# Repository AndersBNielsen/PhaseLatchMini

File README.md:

# PhaseLatch Mini – STM32F103 Dual-ADC IQ USB Streamer

> Combined hardware + firmware + host tooling for a compact dual‑ADC I/Q capture platform.

## Overview

High-rate continuous streaming of interleaved dual ADC (I/Q) samples over USB Full‑Speed (FS) using only the built‑in CDC class on an STM32F103C8 ("Blue Pill" style) board. Companion Python host tools provide live visualization, FIFO bridging, raw capture, diagnostics, and throughput benchmarking.

> Status: Actively optimized. Current configured complex sample rate target: **210.5 k I/Q samples/sec** (`IQ_SAMPLE_RATE_HZ` = 210526) with sustained USB payload throughput >500 KiB/s. Timer PSC/ARR are selected at runtime by a search routine for the closest achievable rate; observed effective rate can be within a small delta of the target. ADC sampling time was reduced (now `ADC_SAMPLETIME_28CYCLES_5`) to reach this rate while maintaining conversion stability.

> Origin / Intended Use: Initially developed as a lightweight streaming engine for the [PhaseLoom](https://github.com/AndersBNielsen/PhaseLoom) project, but fully usable with any dual (I/Q) analog front end producing baseband signals on two STM32F1 ADC channels. 
Note: Phaseloom should be modified for best performance. Replace 22kOhm feedback caps with matched 47kOhm resistors and replace the output stage 50 ohms with 0 ohm. 

---
## Hardware: PhaseLatch Mini
A 4‑layer purple PCB (Blue Pill footprint inspired) integrating two SMA input ports and on‑board ~100 kHz low‑pass filtering (~210 kHz complex baseband bandwidth). Designed around the STM32F103C8 in dual regular simultaneous ADC mode (ADC1 + ADC2) to stream interleaved I/Q samples over USB Full-Speed.

### Key Features
- MCU: STM32F103C8 (72 MHz) LQFP‑48
- Dual simultaneous ADC (12‑bit each) packed into 32‑bit words (I lower 12 bits, Q upper 12 bits)
- 2 × edge‑mount SMA (J20 = I_IN, J21 = Q_IN)
- Integrated passive input filtering (inductor + capacitor network targeting ~100 kHz LPF per channel)
- USB‑C connector (USB2.0 FS, CDC class currently; raw/bulk class option planned)
- On‑board 8 MHz + 32.768 kHz crystals for stable system and RTC timing
- Ferrite bead + local bulk/decoupling for cleaner ADC rails
- Unused GPIOs forced to analog mode early for noise reduction (see `Quiet_Unused_Pins` in `main.c`)
- Headers for expansion / SWD / boot configuration

### Production Assets
All fabrication outputs live in `hardware/PhaseLatchMini/production`:
- `PhaseLatchMini.zip` – Gerber/drill bundle ready for PCB fab
- `bom.csv` – Bill of Materials (with LCSC part numbers for quick JLCPCB sourcing)
- `designators.csv` – Component reference list
- `positions.csv` – Pick‑and‑place XY + rotation for SMT assembly
- `netlist.ipc` – IPC netlist export

Direct link (relative): `hardware/PhaseLatchMini/production/PhaseLatchMini.zip`

### BOM Highlights
Representative components (from `bom.csv`):
- Decoupling: multiple 100 nF 0402 caps (C307331) near MCU and filter sections
- Filter / bulk caps: 22 nF, 220 nF, 470 nF mix shaping input response
- Inductors: six 10 µH (0805) parts forming LC sections for each channel’s low‑pass filtering / supply isolation
- USB-C receptacle: 16‑pin (HCTL HC-TYPE-C-16P-01A) with 5k1 CC resistors for proper orientation detection
- Ferrite bead (FB1) for USB / supply noise suppression
- Voltage regulator: MIC5504-3.3 (SOT‑23‑5) providing clean 3V3
- Crystals: 8 MHz main, 32.768 kHz low‑speed (RTC / optional precise timing)
- SMA edge connectors: matched pair for I and Q inputs

### Assembly Notes
- Clean flux residues near high‑impedance analog nodes (C1/C8 cluster) to keep leakage low.
- If performing hand assembly, solder the SMA edge connectors first to anchor board alignment, then USB, then fine‑pitch MCU.

### Filter Tuning
Current passive network targets ~100 kHz corner. For alternative bandwidths:
- Raise corner: decrease shunt capacitance (e.g., swap 470 nF → 220 nF or 22 nF depending on desired slope) or reduce inductance value.
- Lower corner: increase shunt capacitance or employ higher inductance (space permitting). Recalculate fc ≈ 1/(2π√(L·C_eq)).
- Mitigate source‑resistor induced tilt: include its resistance in design equations; keep initial shunt capacitors modest (≤10 nF) if a 50 Ω series is retained upstream.

## Firmware

- Dual ADC synchronous sampling packed as 32-bit little-endian words (I 12-bit + Q 12-bit inside two 16-bit lanes)
- Target sample rate `IQ_SAMPLE_RATE_HZ` (currently 210526) with dynamic TIM3 prescaler/period search (see `timer_trigger_init()` in `iq_adc.c`)
- ADC sampling time set to `ADC_SAMPLETIME_28CYCLES_5` for higher throughput (previous higher value limited rate)
- Circular DMA with half / full transfer interrupts
- Lock-free ring queue feeding USB transmit path
- ISR burst chaining (current chain limit 16 packets per IN completion) to minimize USB idle gaps
- Immediate DMA IRQ packet scheduling ("kick") to prime first packet of each half-buffer
- Optional diagnostic/stat packets suppressed in throughput builds
- Host tools for diagnostics, throughput, raw capture, FIFO bridging, live view

### Changing the Sample Rate
1. Edit `Inc/iq_adc.h` and set `#define IQ_SAMPLE_RATE_HZ <desired_rate>` (I/Q pairs per second).
2. Ensure the new rate is feasible: TIM3 must be able to realize it given 16-bit ARR and prescaler; the search code picks the closest achievable value.
3. If pushing higher rates:
   - Consider reducing ADC sampling time (`ADC_SAMPLETIME_x`) further, but watch noise/performance.
   - Monitor USB throughput counters (`FEED` command) for increased busy skips.
4. Rebuild and flash. Optionally measure actual achieved rate by counting `iq_dma_half_count` + `iq_dma_full_count` over a timed host interval.

### Verifying Achieved Rate
- After START, issue the `A` command periodically; note increments of half/full counts.
- Effective samples/sec ≈ ((delta_half + delta_full) * half_buffer_samples) / time_interval.
- Or capture a known duration with `host_test.py` and compute rows * rate.

---
## Repository Layout

```
platformio.ini              # Build environments & macro flags
src/                        # Firmware sources (USB, ADC, main logic)
Inc/ / include/             # Public headers
host_*.py                   # Python host utilities
lib/ test/                  # (Placeholders / future use)
```

Key firmware files:
- `src/main.c` – System init, main loop USB feeder (fallback scheduling & instrumentation)
- `src/iq_adc.c` / `Inc/iq_adc.h` – ADC+DMA+Timer configuration, DMA IRQ scheduling kick
- `src/usbd_conf.c` – Low-level USB callbacks, DataIn burst chaining logic
- `src/usbd_cdc_if.c` – CDC interface, command parser (A/F/STATS) & data write API
- `src/usbd_raw.c` (future / optional) – Raw class scaffolding (if transitioning from CDC for additional margin)

Host scripts (root directory):
- `host_diagnostics.py` – Passive capture, STATS delta decode, periodic monitor, USB descriptor info
- `host_throughput.py` – PyUSB bulk endpoint benchmark (raw vendor class / future); shows packet stats
- `host_raw_capture.py` – Robust raw USB (PyUSB or CDC) capture with quiet mode & BrokenPipe safety
- `host_iq_fifo.py` – Serial CDC → named FIFO adapter (u8 or cf32) for GQRX / GNU Radio
- `host_iq_live.py` – Terminal live IQ stats + sparklines / averages
- `host_test.py` – Simple START/STOP based capture, optional float32 output & basic stats
- `host_probe.py` – (Currently empty placeholder for future probing utilities)

---
## Build & Flash (PlatformIO)

Prerequisites:
- VS Code + PlatformIO extension (or `pio` CLI)

Clone & open project, then build one of the defined environments:

### PlatformIO Quickstart (Basics)

If you're new to PlatformIO, these are the minimal steps to get a firmware onto the board.

#### Option A: VS Code GUI
1. Install the "PlatformIO IDE" extension in VS Code.
2. Open this project folder (where `platformio.ini` resides).
3. Bottom status bar: pick the desired environment (e.g. `adc`).
4. Click the checkmark (Build). Wait for success.
5. Connect the board via USB (ensure it enumerates) and press the right arrow (Upload). If first flash fails, press/hold BOOT (if available) or use a serial/USB boot jumper sequence depending on your Blue Pill variant.
6. Use the plug icon (Monitor) or run a host script to interact.

#### Option B: CLI
Install PlatformIO Core (Python 3.11+ recommended):
```bash
pip install --upgrade platformio
```
From the project root:
```bash
# List environments defined in platformio.ini
pio run --list-targets

# Build the adc environment
pio run -e adc

# Upload (adjust -e if choosing another env)
pio run -e adc -t upload

# Open a serial monitor (Ctrl+C to exit)
pio device monitor -b 115200
```
If you see permission errors on macOS/Linux, you may need to adjust USB device permissions or add your user to the appropriate group (e.g. `dialout` on some Linux distros).

#### Common Upload Notes
- Some Blue Pill clones require setting/removing BOOT0 jumpers for the built-in ROM bootloader; after initial flash with a USB‑TTL adapter or ST-Link, subsequent USB CDC updates normally proceed automatically.
- For ST-Link users, ensure drivers and udev rules (Linux) are installed.
- If the device does not reset into the new firmware, press the hardware RESET button.

#### Serial Device Identification
On macOS you'll typically see `/dev/tty.usbmodem*`. On Linux, it may appear as `/dev/ttyACM0`. Use `pio device list` to enumerate.

Environments (see `platformio.ini`):
- `env:baseline` – Minimal USB baseline with reduced diagnostics (throughput focus pattern)
- `env:diag` – Heavier diagnostics enabled (ASCII stat chatter)
- `env:adc` – Active dual-ADC streaming (ENABLE_IQ + throughput suppressions)
- `env:adc_smoke` – Lower-intensity validation (extra ADC status prints)

Typical flow (using `env:adc`):
1. Select `adc` environment in PlatformIO
2. Build (should report flash usage ~30%, RAM ~55%)
3. Upload (DFU/serial depending on board configuration)
4. Open a serial monitor or run a host script (e.g. `python host_test.py --progress`)

If enumeration stalls: power cycle board or press reset. Heartbeat LED indicates main loop alive; rapid fallback pattern indicates SysTick/USB early issues.

---
## Runtime Commands (CDC)

Send as ASCII (line ending flexible, CR/LF accepted):
- `START` – Begin IQ streaming (if not already running)
- `STOP` – Halt streaming (host_test.py sends on exit)
- `A` – Print `ADCSTAT` line with ADC & DMA counters
- `F` – Print `FEED` line (USB feeder instrumentation)
- `STATS` – Legacy status snapshot (may be suppressed in throughput builds)

---
## Data Format

Each IQ sample pair is one 32-bit little-endian word composed of two 16‑bit containers produced by the STM32F1 dual regular simultaneous ADC mode:
```
Bits  0..11  : I (ADC1 12-bit result, right-aligned)
Bits 12..15  : Unused (always 0)  <-- upper 4 bits of lower 16-bit half-word
Bits 16..27  : Q (ADC2 12-bit result, right-aligned)
Bits 28..31  : Unused (always 0)  <-- upper 4 bits of upper 16-bit half-word
```

So effectively:
```
uint16_t I_lane = word & 0xFFFF;          // lower half-word
uint16_t Q_lane = (word >> 16) & 0xFFFF;  // upper half-word
uint16_t I_raw12 = I_lane & 0x0FFF;       // mask to 12 bits
uint16_t Q_raw12 = Q_lane & 0x0FFF;
```

The current `host_test.py` treats each 16-bit lane as a full-range unsigned sample and subtracts 32768. That overstates magnitude and uses the high (always zero) 4 bits. For correct 12‑bit centered scaling use:
```
float I = ((int)I_raw12 - 2048) / 2048.0f;   // ≈ [-1.0, +1.0)
float Q = ((int)Q_raw12 - 2048) / 2048.0f;
```
If you need signed 16-bit containers for downstream tooling, you can expand by left-shifting 4 (to occupy high bits) or replicate into 16-bit signed with:
```
int16_t I_s16 = ((int16_t)(I_raw12 ^ 0x800) - 0x800) << 4; // optional dynamic range padding
```
But most host paths should just mask & center at 2048.

---
## ADC / Timing Configuration

- Timer configuration is dynamic: `timer_trigger_init()` iterates prescaler values to find an ARR producing a rate closest to `IQ_SAMPLE_RATE_HZ`.
- Current target: 210526 samples/sec (complex pairs). Achieved rate is printed only via manual inspection (no direct text output yet); you can instrument `(best_rate)` variable in debugger if needed.
- ADC sampling time currently `ADC_SAMPLETIME_28CYCLES_5`; lowering further increases throughput but may degrade SNR and settling for higher source impedances.

Potential Adjustments:
- Increase `IQ_SAMPLE_RATE_HZ` (watch USB bandwidth & chain limit utilization).
- Change ADC sampling time for performance vs accuracy trade-off.
- Raise `chain_limit` (in `usbd_conf.c`) beyond 16 if the queue frequently stalls with residual samples and main loop fallback is minimal.

---
## USB Transfer Strategy & Optimizations
- Chain limit now 16 (see `usbd_conf.c`); README previously referenced 12—updated.
- DMA IRQ kick ensures first packet of each half-buffer is scheduled promptly.
- Remaining headroom: adopt packed 3-byte I12|Q12 mode (roadmap) or vendor RAW class for further rate increases.

---
## Instrumentation & Monitoring

Example FEED output (command `F`):
```
FEED loop=12345 isr=67890 busy=12 chain_max=11
```
Where:
- `loop` – Packets scheduled from main loop (fallback)
- `isr` – Packets scheduled from ISR path (burst + DMA kick)
- `busy` – Attempts skipped because endpoint currently active
- `chain_max` – Highest contiguous packets chained in a single IN completion

ADCSTAT example (`A`):
```
ADCSTAT half=1024 full=1024 drops=0
```
(Exact field names may vary—check live output.)

Use `host_diagnostics.py stats` for legacy STAT delta interpretation, if enabled in build.

---
## Host Utilities

| Script | Purpose |
|--------|---------|
| `host_test.py` | Simple START capture, optional float32 output, stats, graceful Ctrl+C |
| `host_iq_live.py` | Real-time terminal IQ level display, window averages, sparkline |
| `host_iq_fifo.py` | Serial → FIFO converter (u8 or cf32) for GQRX / fifo consumers |
| `host_raw_capture.py` | Raw byte dump with quiet & BrokenPipe-safe pipeline support |
| `host_diagnostics.py` | STATS deltas, passive capture, USB descriptor info |
| `host_throughput.py` | High-rate PyUSB bulk benchmark (raw class future) |
| `host_probe.py` | Placeholder for future probing tools |

### GQRX Integration (via FIFO)
- Set GQRX sample rate to match `IQ_SAMPLE_RATE_HZ` (e.g. 210526) or the nearest supported value.
1. Run FIFO bridge:
   ```
   python3 host_iq_fifo.py --fifo /tmp/iq_cf32.iq
   ```
2. In GQRX, set input to "UDP / File" or external source capable of reading named FIFO (Linux/macOS). Point to `/tmp/iq_cf32.fifo` with sample rate = `210526`.
3. Adjust gain/AGC in GQRX; confirm spectrum updates.

### Live View
```
python host_iq_live.py --port /dev/tty.usbmodemXYZ --window 512 --spark --interval 0.2
```
Shows min/max, window & running averages, and a small ASCII sparkline.

### Raw Capture Example
```
python host_raw_capture.py --out stream.bin --secs 5 --quiet
```
Then post-process with custom scripts or convert to complex floats.

---
## Performance Measurement

Quick rate check (CDC path):
```
python host_test.py --seconds 3 --progress
```
Or FEED counters before & after a timed interval to estimate packet dispatch accumulation.

PyUSB high-rate test (when using/adding raw vendor class):
```
python host_throughput.py --seconds 5 --progress
```

Interpretation updates:
- Bytes/sec ÷ 4 = complex samples/sec (current raw 32-bit mode).
- For future 3-byte packed mode bytes/sec ÷ 3 will apply.

---
## Troubleshooting

| Symptom | Suggestions |
|---------|-------------|
| No `/dev/tty.usbmodem*` device | Replug USB, check cable, ensure board enumerates (dmesg / system log) |
| Streaming stalls after START | Check FEED counters (isr incrementing?). Confirm no flood of diagnostics enabled. |
| Throughput lower than expected | Ensure running `env:adc` (not `diag`), verify chain_max near limit, reduce host-side latency (no heavy printing) |
| Mis-scaled IQ values | Mask to 12 bits (0x0FFF) before centering; ensure not interpreting high unused bits |
| Broken pipe in pipeline capture | Use `host_raw_capture.py --quiet` (handles SIGPIPE and flush safety) |

---
## Roadmap / Future Ideas
- Maintain or push beyond 210 kS/s (USB packing & endpoint tuning)
- Optional tighter 24-bit (3-byte) packing (I12|Q12) – reduces bandwidth ~25%
- Vendor RAW class endpoint for marginal gains over CDC ACM
- Lightweight CRC / sequence tags for host-side drop detection
- Optional AGC / scaling in firmware (convert to centered 16-bit signed)
- Continuous integration tests for host scripts
- IQ gain/phase auto-calibration
- Expanded PhaseLatch Mini variants (higher‑resolution MCUs, external HS USB)

## License

(Choose and add a SPDX license header & file as appropriate, e.g. MIT or Apache-2.0.)

---
## Attribution / Notes

Developed as an incremental exploration of practical FS USB throughput & latency reduction techniques on resource-constrained MCUs while streaming synchronous dual-ADC data.

Contributions / suggestions welcome.

## Getting a PCB

## Production & Manufacturing
- The `hardware/production/` folder includes all needed files. 

This project is kindly sponsored by JLCPCB. They offer cheap, professional looking PCBs and super fast delivery.

Step 1: Get the gerber file zip package from the /hardware folder

Step 2: Upload to JLCPCB [https://jlcpcb.com/?from=Anders_N](https://jlcpcb.com/?from=Anders_N)

Step 3: Pick your color, surface finish and order.

You can use these affiliate links to get a board for $2 and also get $54 worth of New User Coupons at: https://jlcpcb.com/?from=Anders_N

And in case you also want to order a 3D-printed case you can use this link. 
How to Get a $7 3D Printing Coupon: [https://3d.jlcpcb.com/?from=Anders3DP](https://jlc3dp.com/?from=Anders_N)

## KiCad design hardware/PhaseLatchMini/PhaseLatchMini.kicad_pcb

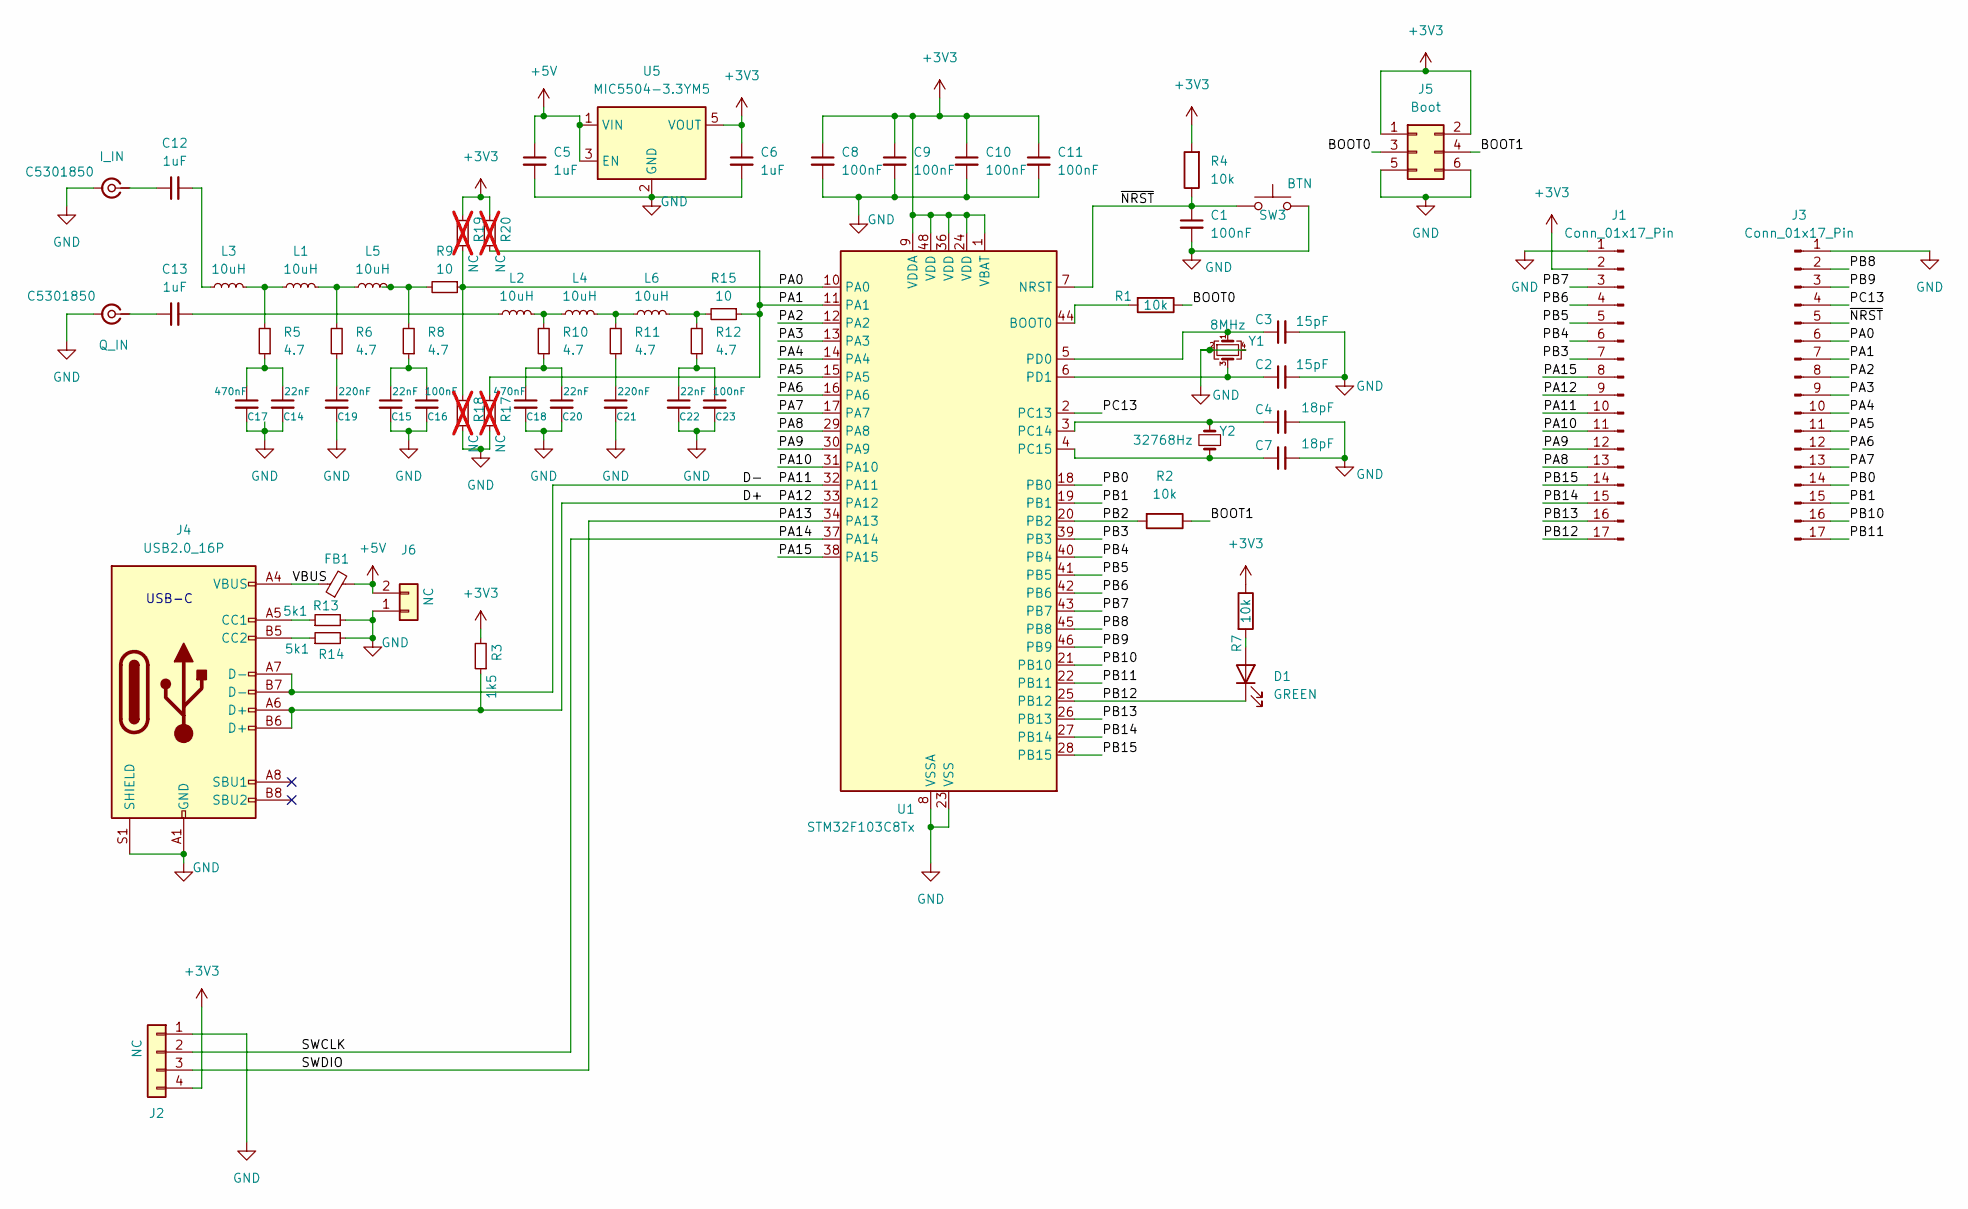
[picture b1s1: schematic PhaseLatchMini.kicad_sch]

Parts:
C1, C8, C9, C10, C11, C16, C23: 100nF; C_0402_1005Metric; LCSC C307331
C2, C3: 15pF; C_0402_1005Metric; LCSC C1548
C4, C7: 18pF; C_0402_1005Metric; LCSC C1549
C5, C6, C12, C13: 1uF; C_0805_2012Metric; LCSC C28323
C14, C15, C20, C22: 22nF; C_0402_1005Metric; LCSC C1532
C17, C18: 470nF; C_0603_1608Metric; LCSC C1623
C19, C21: 220nF; C_0402_1005Metric; LCSC C16772
D1: GREEN; LED_0805_2012Metric; LCSC C2297
FB1: FerriteBead_Small; L_0603_1608Metric; LCSC C14709
J1, J3: Conn_01x17_Pin; PinHeader_1x17_P2.54mm_Vertical
J2: NC; PinHeader_1x04_P2.54mm_Vertical
J4: USB2.0_16P; USB_C_Receptacle_HCTL_HC-TYPE-C-16P-01A; LCSC C2894897
J5: Boot; PinHeader_2x03_P2.54mm_Vertical
J6: NC; PinHeader_1x02_P2.54mm_Vertical
J20: I_IN; SMA_Samtec_SMA-J-P-H-ST-EM1_EdgeMount; LCSC C5301850
J21: Q_IN; SMA_Samtec_SMA-J-P-H-ST-EM1_EdgeMount; LCSC C5301850
L1, L2, L3, L4, L5, L6: 10uH; L_0805_2012Metric; LCSC C1046
R1, R2, R4, R7: 10k; R_0402_1005Metric; LCSC C25744
R3: 1k5; R_0402_1005Metric; LCSC C25867
R5, R6, R8, R10, R11, R12: 4.7; R_0603_1608Metric; LCSC C23164
R9, R15: 10; R_0603_1608Metric; LCSC C22859
R13, R14: 5k1; R_0402_1005Metric; LCSC C25905
R17, R18, R19, R20: NC; R_0402_1005Metric; LCSC C25867; not fitted
SW3: BTN; SW_SPST_TL3342; LCSC C318884
U1: STM32F103C8Tx; LQFP-48_7x7mm_P0.5mm; LCSC C8734
U5: MIC5504-3.3YM5; SOT-23-5; LCSC C3021093
Y1: 8MHz; Crystal_SMD_3225-4Pin_3.2x2.5mm; LCSC C5308002
Y2: 32768Hz; Crystal_SMD_3215-2Pin_3.2x1.5mm; LCSC C32346

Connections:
+3V3: C6.1, C8.1, C9.1, C10.1, C11.1, J1.2, J2.4, J5.1, J5.2, R3.2, R4.2, R7.1, R19.2, R20.2, U1.1 (VBAT), U1.9 (VDDA), U1.24 (VDD), U1.36 (VDD), U1.48 (VDD), U5.5 (VOUT)
+5V: C5.1, FB1.2, J6.2, U5.1 (VIN), U5.3 (EN)
/BOOT0: J5.3, R1.1
/BOOT1: J5.4, R2.1
/D+: J1.9, J4.A6 (D+), J4.B6 (D+), R3.1, U1.33 (PA12)
/D-: J1.10, J4.A7 (D-), J4.B7 (D-), U1.32 (PA11)
/PA0: J3.6, R9.1, R18.2, R19.1, U1.10 (PA0)
/PA1: J3.7, R15.1, R17.2, R20.1, U1.11 (PA1)
/PA2: J3.8, U1.12 (PA2)
/PA3: J3.9, U1.13 (PA3)
/PA4: J3.10, U1.14 (PA4)
/PA5: J3.11, U1.15 (PA5)
/PA6: J3.12, U1.16 (PA6)
/PA7: J3.13, U1.17 (PA7)
/PA8: J1.13, U1.29 (PA8)
/PA9: J1.12, U1.30 (PA9)
/PA10: J1.11, U1.31 (PA10)
/PA13: J2.3, U1.34 (PA13)
/PA14: J2.2, U1.37 (PA14)
/PA15: J1.8, U1.38 (PA15)
/PB0: J3.14, U1.18 (PB0)
/PB1: J3.15, U1.19 (PB1)
/PB2: R2.2, U1.20 (PB2)
/PB3: J1.7, U1.39 (PB3)
/PB4: J1.6, U1.40 (PB4)
/PB5: J1.5, U1.41 (PB5)
/PB6: J1.4, U1.42 (PB6)
/PB7: J1.3, U1.43 (PB7)
/PB8: J3.2, U1.45 (PB8)
/PB9: J3.3, U1.46 (PB9)
/PB10: J3.16, U1.21 (PB10)
/PB11: J3.17, U1.22 (PB11)
/PB12: D1.1 (K), J1.17, U1.25 (PB12)
/PB13: J1.16, U1.26 (PB13)
/PB14: J1.15, U1.27 (PB14)
/PB15: J1.14, U1.28 (PB15)
/PC13: J3.4, U1.2 (PC13)
/VBUS: FB1.1, J4.A4 (VBUS), J4.A9 (VBUS), J4.B4 (VBUS), J4.B9 (VBUS)
/~NRST: C1.1, J3.5, R4.1, SW3.1, U1.7 (NRST)
GND: C1.2, C2.2, C3.2, C4.2, C5.2, C6.2, C7.2, C8.2, C9.2, C10.2, C11.2, C14.2, C15.2, C16.2, C17.2, C18.2, C19.2, C20.2, C21.2, C22.2, C23.2, J1.1, J2.1, J3.1, J4.A1 (GND), J4.A12 (GND), J4.B1 (GND), J4.B12 (GND), J4.S1 (SHIELD), J5.5, J5.6, J6.1, J20.2 (Ext), J21.2 (Ext), R13.2, R14.2, R17.1, R18.1, SW3.2, U1.8 (VSSA), U1.23 (VSS), U1.35 (VSS), U1.47 (VSS), U5.2 (GND), Y1.2, Y1.4
unnamed: C12.2, L3.1
unnamed: C13.2, L2.1
unnamed: C14.1, C17.1, R5.1
unnamed: C15.1, C16.1, R8.1
unnamed: C18.1, C20.1, R10.1
unnamed: C19.1, R6.1
unnamed: C21.1, R11.1
unnamed: C22.1, C23.1, R12.1
unnamed: D1.2 (A), R7.2
unnamed: J4.A5 (CC1), R13.1
unnamed: J4.B5 (CC2), R14.1
unnamed: C12.1, J20.1 (In)
unnamed: C13.1, J21.1 (In)
unnamed: L1.1, L3.2, R5.2
unnamed: L1.2, L5.1, R6.2
unnamed: L2.2, L4.1, R10.2
unnamed: L4.2, L6.1, R11.2
unnamed: L5.2, R8.2, R9.2
unnamed: L6.2, R12.2, R15.2
unnamed: R1.2, U1.44 (BOOT0)
unnamed: C4.1, U1.3 (PC14), Y2.2
unnamed: C7.1, U1.4 (PC15), Y2.1
unnamed: C3.1, U1.5 (PD0), Y1.1
unnamed: C2.1, U1.6 (PD1), Y1.3

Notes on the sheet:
USB-C

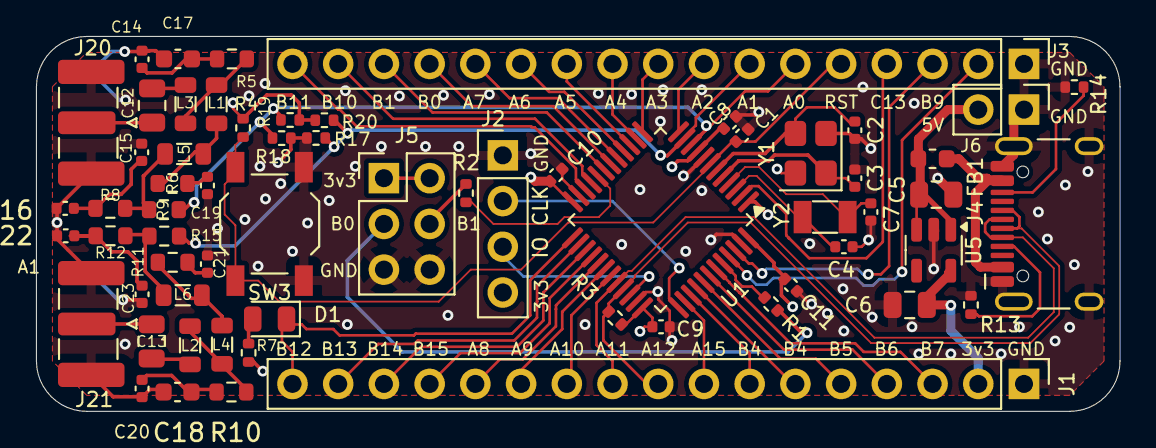
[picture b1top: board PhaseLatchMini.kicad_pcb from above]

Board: 4 copper layers, 60.2 x 20.8 mm, 63 parts (0 on the bottom side), 64 nets.

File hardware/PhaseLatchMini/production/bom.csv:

Designator,Footprint,Quantity,Value,LCSC Part #
"C1, C10, C11, C16, C23, C8, C9",0402,7,100nF,C307331
"C12, C13, C5, C6",0805,4,1uF,C28323
"C14, C15, C20, C22",0402,4,22nF,C1532
"C17, C18",0603,2,470nF,C1623
"C19, C21",0402,2,220nF,C16772
"C2, C3",0402,2,15pF,C1548
"C4, C7",0402,2,18pF,C1549
D1,0805,1,GREEN,C2297
FB1,0603,1,FerriteBead_Small,C14709
"J1, J3",PinHeader_1x17_P2.54mm_Vertical,2,Conn_01x17_Pin,
J2,PinHeader_1x04_P2.54mm_Vertical,1,NC,
J20,SMA_Samtec_SMA-J-P-H-ST-EM1_EdgeMount,1,I_IN,C5301850
J21,SMA_Samtec_SMA-J-P-H-ST-EM1_EdgeMount,1,Q_IN,C5301850
J4,USB_C_Receptacle_HCTL_HC-TYPE-C-16P-01A,1,USB2.0_16P,C2894897
J5,PinHeader_2x03_P2.54mm_Vertical,1,Boot,
J6,PinHeader_1x02_P2.54mm_Vertical,1,NC,
"L1, L2, L3, L4, L5, L6",0805,6,10uH,C1046
"R1, R2, R4, R7",0402,4,10k,C25744
"R10, R11, R12, R5, R6, R8",0603,6,4.7,C23164
"R13, R14",0402,2,5k1,C25905 
"R15, R9",0603,2,10,C22859
"R17, R18, R19, R20",0402,4,NC,C25867
R3,0402,1,1k5,C25867
SW3,SW_SPST_TL3342,1,BTN,C318884
U1,LQFP-48_7x7mm_P0.5mm,1,STM32F103C8Tx,C8734
U5,SOT-23-5,1,MIC5504-3.3YM5,C3021093
Y1,Crystal_SMD_3225-4Pin_3.2x2.5mm,1,8MHz,C5308002
Y2,Crystal_SMD_3215-2Pin_3.2x1.5mm,1,32768Hz,C32346

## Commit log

2025-10-02 Silk
2025-10-21 Almost ready for initial release
2025-11-15 Pin platfrom version for reproducable results
